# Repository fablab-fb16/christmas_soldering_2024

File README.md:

# 🎄 Christmas Soldering 2024 🎄

Home of the Christmas Soldering project for 2024.

You will find everything you need to build your own in here.

---

## 👀 Overview

**Hardware:** Custom PCB with **ESP-C3-SUPERMINI** and addressable **RGB LEDs**.
Designed by Janos Föth.

**Software:** The awesome [WLED](https://github.com/Aircoookie/WLED) for an easy start to get lights blinking. (we got a pre-configured version for you)

### ✨ Features

- **Interactive**: Change light patterns using the button or via WiFi / App.
- **Extensible**: Add a microphone to make the LEDs blink to the beat of music, integrate it with your smart home or write your own custom code to control the blinking.
- **Festive**: A glowing, Christmas tree-themed project perfect for the holidays.

---

## 📚 Quick Start

Find step-by-step instructions here, if you already have the soldering-kit at hand:

- [Detaillierte Anleitung (DE)](/documentation/Build%20Instructions%20DE.md)
- [Detailed Assembly Instructions (EN)](/documentation/Build%20Instructions%20EN.md)
- For beginners in soldering: [How to Solder Guide](/documentation/How%20to%20Solder.md)

---

## 🛠 How to Build Your Own from Scratch

You can order the parts and build the blinking tree totally on your own.

1. See the [Hardware Instructions](/pcb_christmas_soldering_kit/Hardware_Instructions.md) for a list of needed parts and instructions on how to order the board (PCB).
2. When you have the ESP32 at hand, follow [Software Instructions](/WLED_Firmware/Readme.md) to get the WLED firmware flashed. We have a pre-configured version for the soldering kit that you just need to flash.
3. Solder the kit, following the [Detailed Assembly Instructions (EN)](/documentation/Build%20Instructions%20EN.md) / [Detaillierte Anleitung (DE)](/documentation/Build%20Instructions%20DE.md)
4. Enjoy the lights.

---

## 👩‍🏭 Usage at Soldering Workshops

This kit was developed for a soldering workshop and therefore to be solder-beginner-friendly.

Feel free to use it for your own soldering workshops. If you got ideas for improvement or feedback, please let us know e.g. via a github issue or email at 

For getting a large amount of ESPs flashed efficiently, we developed a flash script plus the support to print the unique SSID+PW of each ESP on small labels with Brother QL Label Printers directly after flashing. Find instructions for it [here](/WLED_Firmware/Readme.md). This way, everyone at the event knows which Wifi Access Point belongs to the own Blinking Tree.

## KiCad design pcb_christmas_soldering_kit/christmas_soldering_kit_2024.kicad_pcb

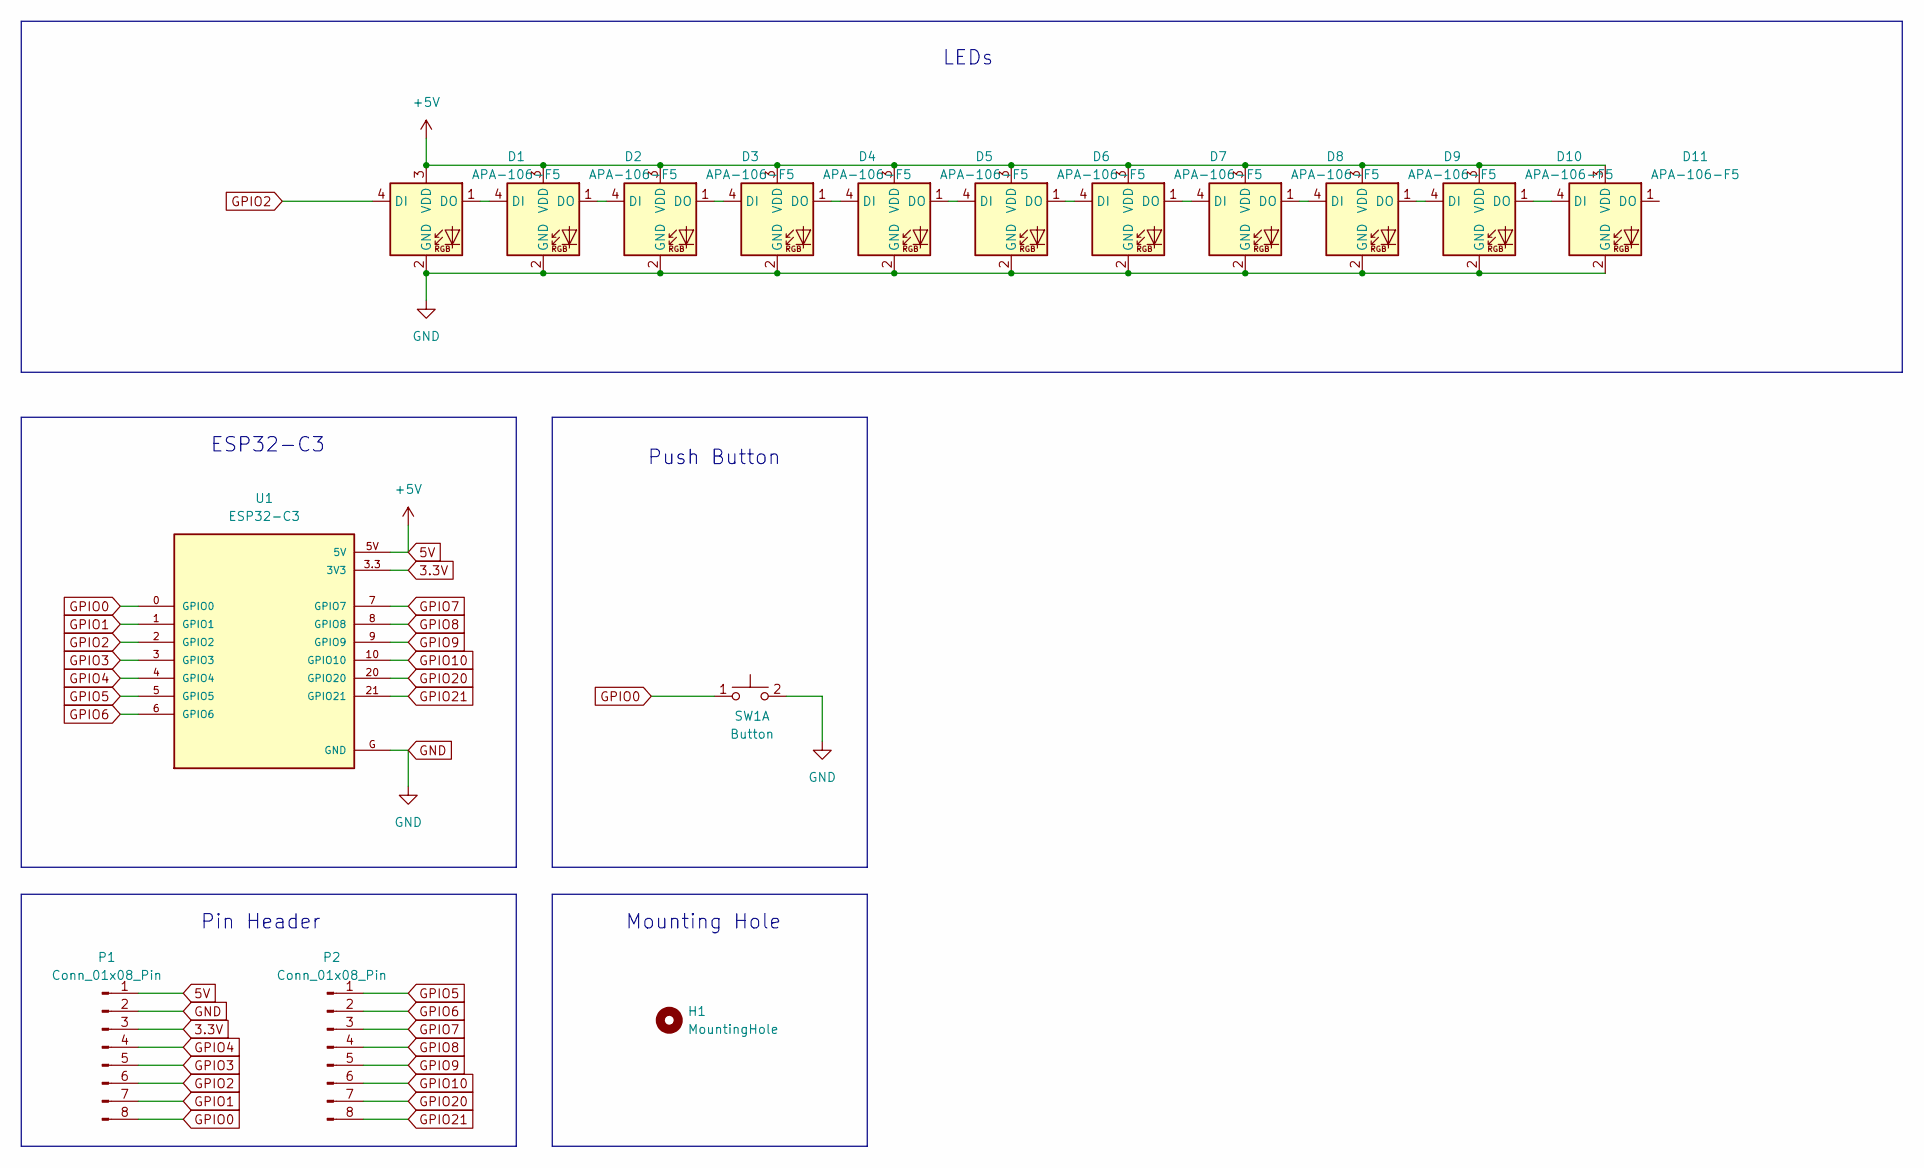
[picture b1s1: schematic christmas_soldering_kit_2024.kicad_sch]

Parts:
D1, D2, D3, D4, D5, D6, D7, D8, D9, D10, D11: APA-106-F5; LED_D5.0mm-4_RGB
H1: MountingHole; MountingHole_2.2mm_M2
P1, P2: Conn_01x08_Pin; PinHeader_1x08_P2.54mm_Vertical
SW1: Button; SW_PUSH_6mm
U1: ESP32-C3; MODULE_ESP32-C3_SUPERMINI

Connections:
3.3V: P1.3, U1.3.3 (3V3)
5V: D1.3 (VDD), D2.3 (VDD), D3.3 (VDD), D4.3 (VDD), D5.3 (VDD), D6.3 (VDD), D7.3 (VDD), D8.3 (VDD), D9.3 (VDD), D10.3 (VDD), D11.3 (VDD), P1.1, U1.5V
GND: D1.2 (GND), D2.2 (GND), D3.2 (GND), D4.2 (GND), D5.2 (GND), D6.2 (GND), D7.2 (GND), D8.2 (GND), D9.2 (GND), D10.2 (GND), D11.2 (GND), P1.2, SW1.2 (D), U1.G (GND)
GPIO0: P1.8, SW1.1 (C), U1.0 (GPIO0)
GPIO1: P1.7, U1.1 (GPIO1)
GPIO2: D1.4 (DI), P1.6, U1.2 (GPIO2)
GPIO3: P1.5, U1.3 (GPIO3)
GPIO4: P1.4, U1.4 (GPIO4)
GPIO5: P2.1, U1.5 (GPIO5)
GPIO6: P2.2, U1.6 (GPIO6)
GPIO7: P2.3, U1.7 (GPIO7)
GPIO8: P2.4, U1.8 (GPIO8)
GPIO9: P2.5, U1.9 (GPIO9)
GPIO10: P2.6, U1.10 (GPIO10)
GPIO20: P2.7, U1.20 (GPIO20)
GPIO21: P2.8, U1.21 (GPIO21)
unnamed: D1.1 (DO), D2.4 (DI)
unnamed: D2.1 (DO), D3.4 (DI)
unnamed: D3.1 (DO), D4.4 (DI)
unnamed: D4.1 (DO), D5.4 (DI)
unnamed: D5.1 (DO), D6.4 (DI)
unnamed: D6.1 (DO), D7.4 (DI)
unnamed: D7.1 (DO), D8.4 (DI)
unnamed: D8.1 (DO), D9.4 (DI)
unnamed: D9.1 (DO), D10.4 (DI)
unnamed: D10.1 (DO), D11.4 (DI)

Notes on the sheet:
Mounting Hole
LEDs
ESP32-C3
Pin Header
Push Button

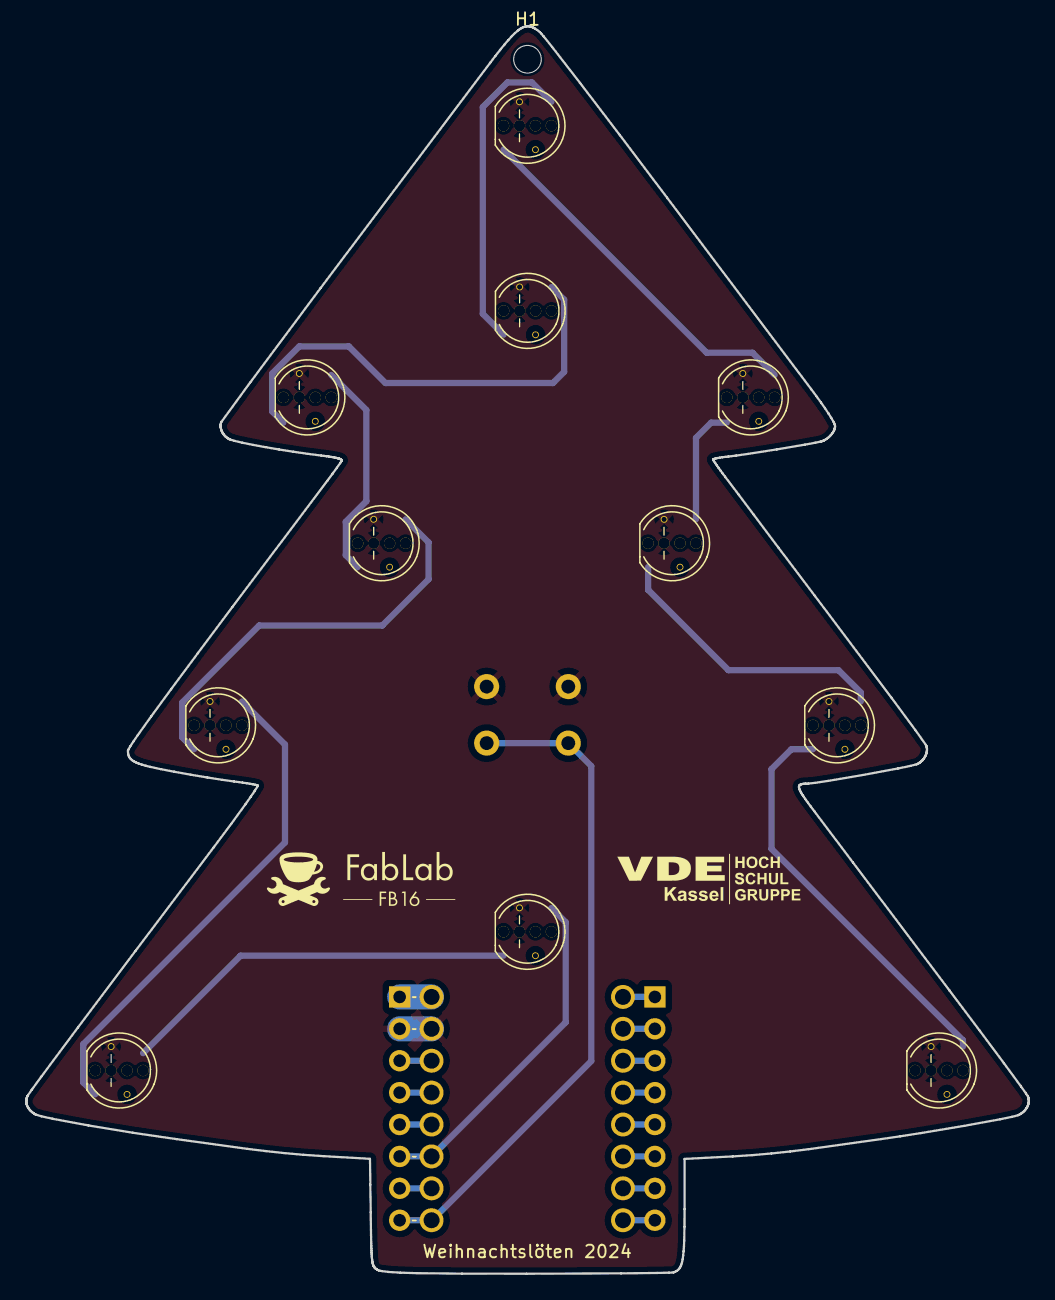
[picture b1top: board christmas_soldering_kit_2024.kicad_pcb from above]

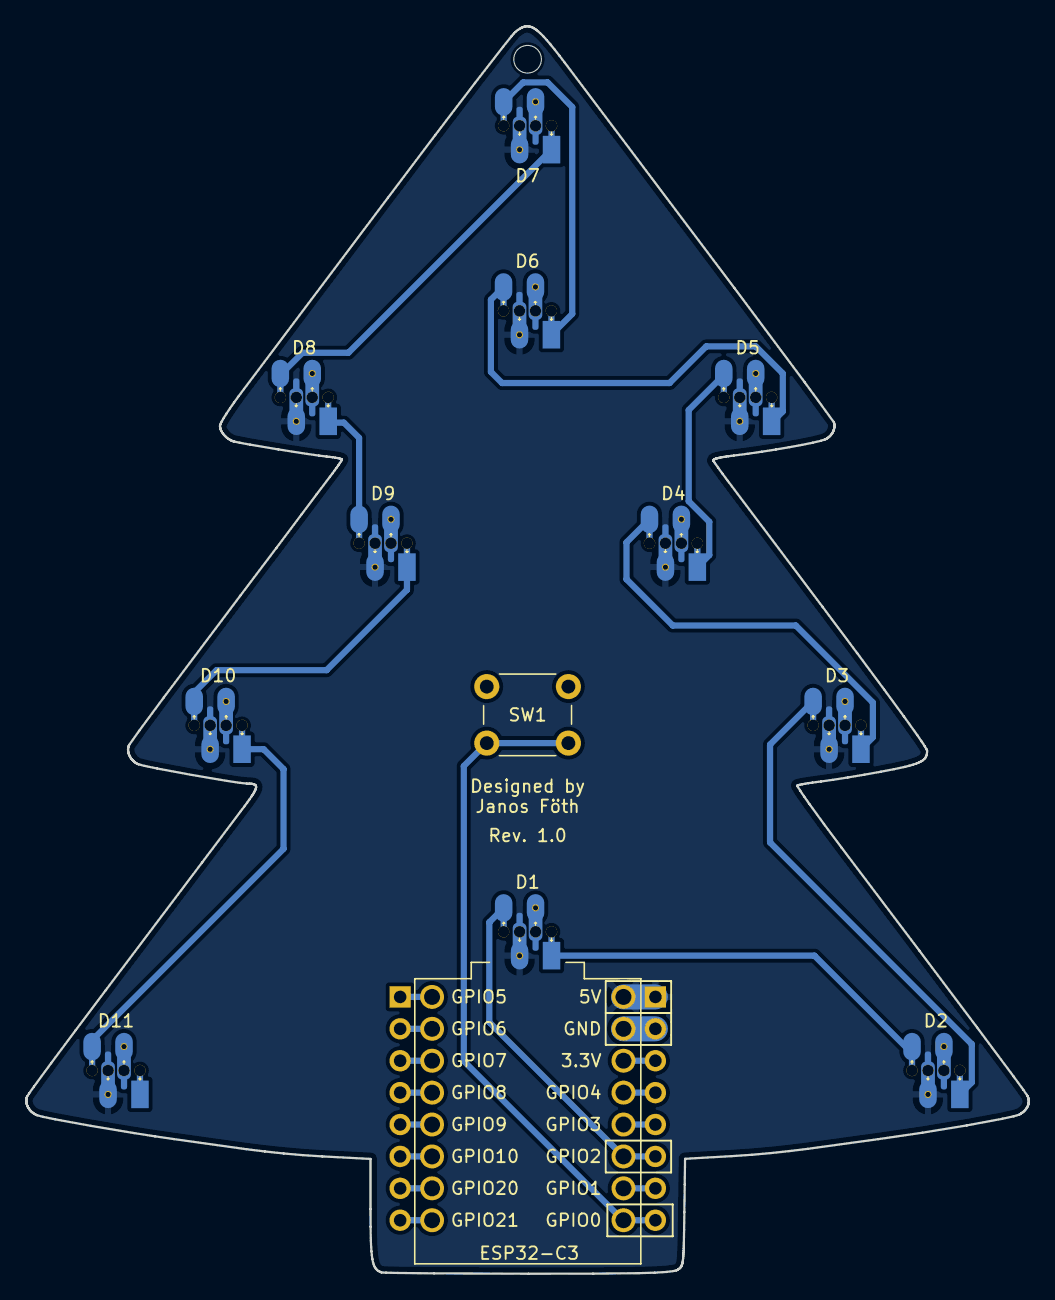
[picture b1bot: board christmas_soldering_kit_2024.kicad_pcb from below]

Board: 2 copper layers, 79.8 x 99.3 mm, 16 parts (4 on the bottom side), 26 nets.

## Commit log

2024-11-25 Add ordered prototype version of PCB
2024-11-25 add draft of readme
2024-11-27 prototype 2: remove unnecessary components, improve LED footprints
2024-11-27 prototype 2.1: maybe? fixed led footprint for production
2024-11-29 Added custom Christmas soldering firmware based on the WLED firmware Added script to install firmware on ESP32-C3
2024-11-29 Added Description for WLED Firmware
2024-11-29 Added English Version of WLED Firmware Readme
2024-11-29 Corrected Headlines
2024-11-29 Revert "Corrected Headlines"
    This reverts commit 7e8dd513406acc5dd140db70135cada3d621c0a2.
2024-12-04 prototype 2 (ordered)
2024-12-04 final version, rev. 1.0: ordered
2024-12-05 Updated Firmware and Install Script (Macros for Button push are now implemented)
2024-12-06 images upload and first draft
2024-12-07 Updating images and uploading the instructions in german as a pdf
2024-12-07 Uploading the english version
2024-12-07 correcting the name of the en pdf in readme
2024-12-07 small detail in readme
2024-12-07 adding markdown file, putting the pdfs aside for download
2024-12-07 adding the english version
2024-12-07 creating readme to the documentation
2024-12-07 small edit on main page
2024-12-07 wrote Features to main page and changed design
2024-12-07 Correct spelling
2024-12-07 removing double (DE) (EN)
2024-12-09 add label printer scipts
2024-12-11 anleitung
    adding images, removing the pdfs, editing the Anleitung (DE), the instructions (EN) and editing /main/README
2024-12-11 QR-Codes upload
2024-12-11 last edits
2024-12-11 Script for label printer added to Install script
2024-12-11 Instructions for self-installation of firmware added to Readme.md
2024-12-11 Correction Readme.md
2024-12-11 final ordered PCB version
2024-12-11 remove .DS_Store files and add them to gitignore
2024-12-11 add Hardware Instructions
2024-12-11 update main readme
2024-12-12 update: how to solder
2024-12-12 update: label printer instuctions
2024-12-12 update: Build Instructions DE
2024-12-12 try to fix duplicate folder issue: move docs to temp folder
2024-12-12 try to fix duplicate folder issue: move back to documentation folder
2024-12-12 fix broken image links
2024-12-12 update images
2024-12-12 update image width in Instructions
2024-12-12 Update Readme.md: add links to custom WLED Repo
